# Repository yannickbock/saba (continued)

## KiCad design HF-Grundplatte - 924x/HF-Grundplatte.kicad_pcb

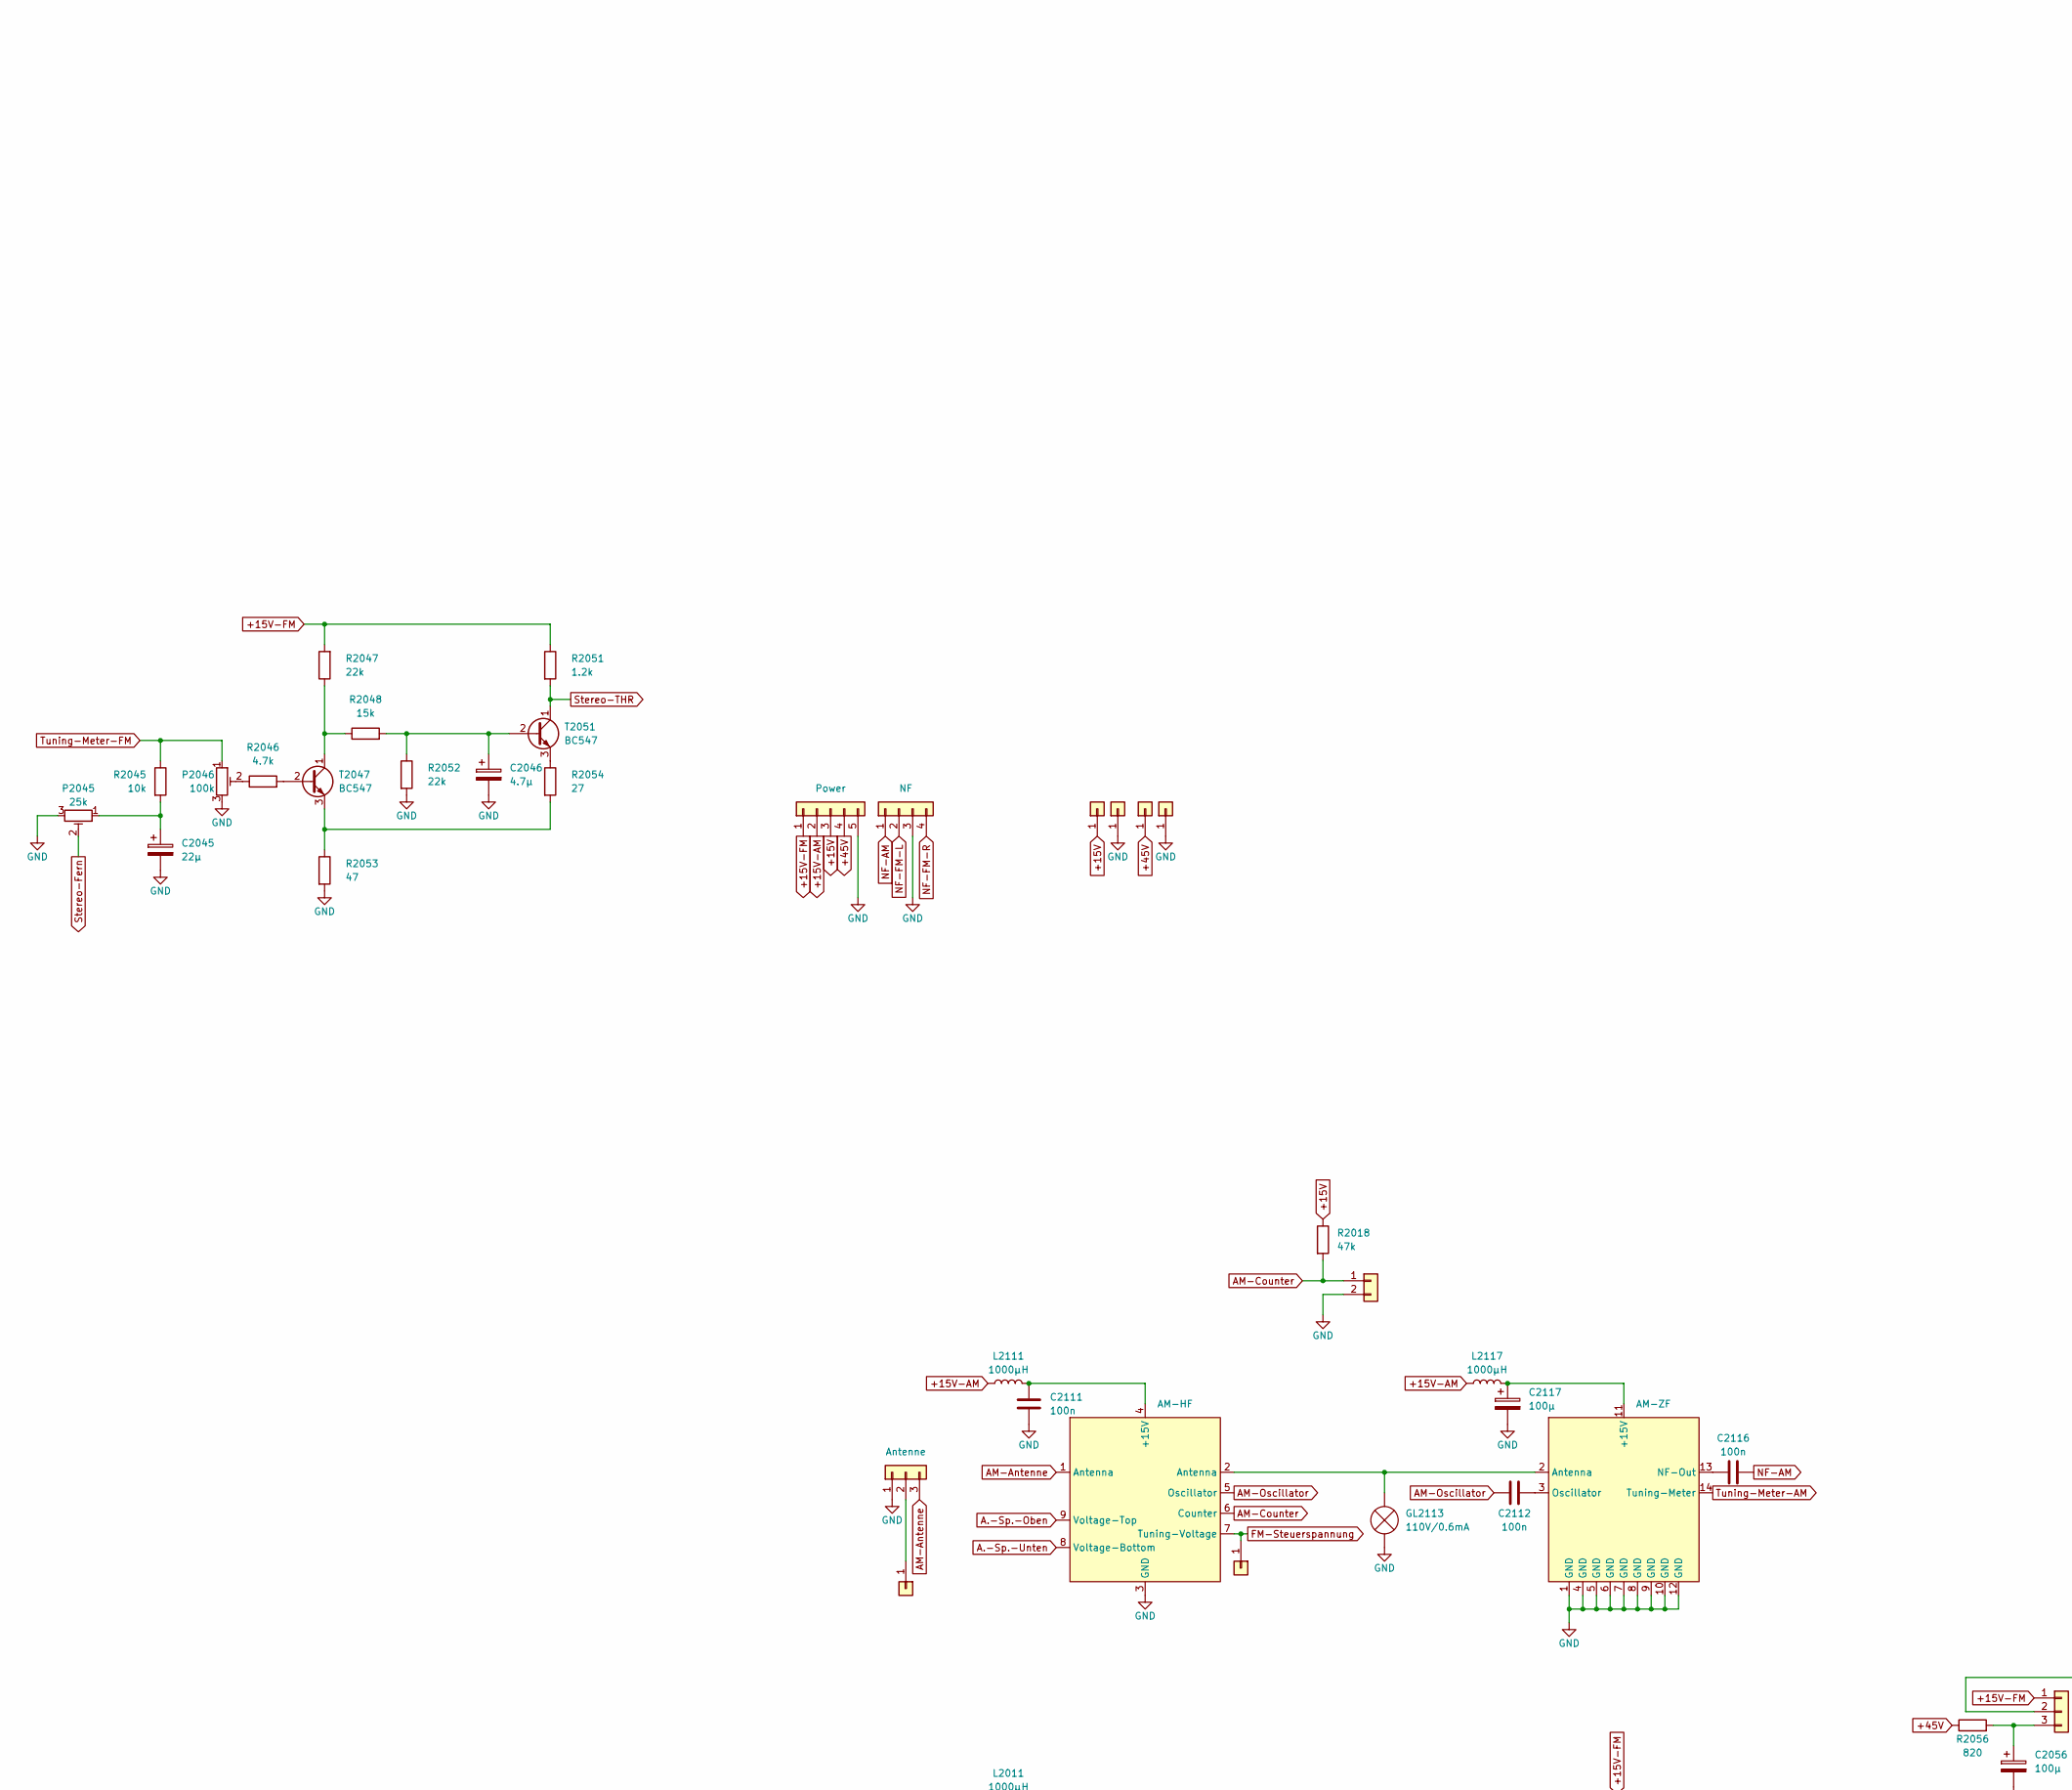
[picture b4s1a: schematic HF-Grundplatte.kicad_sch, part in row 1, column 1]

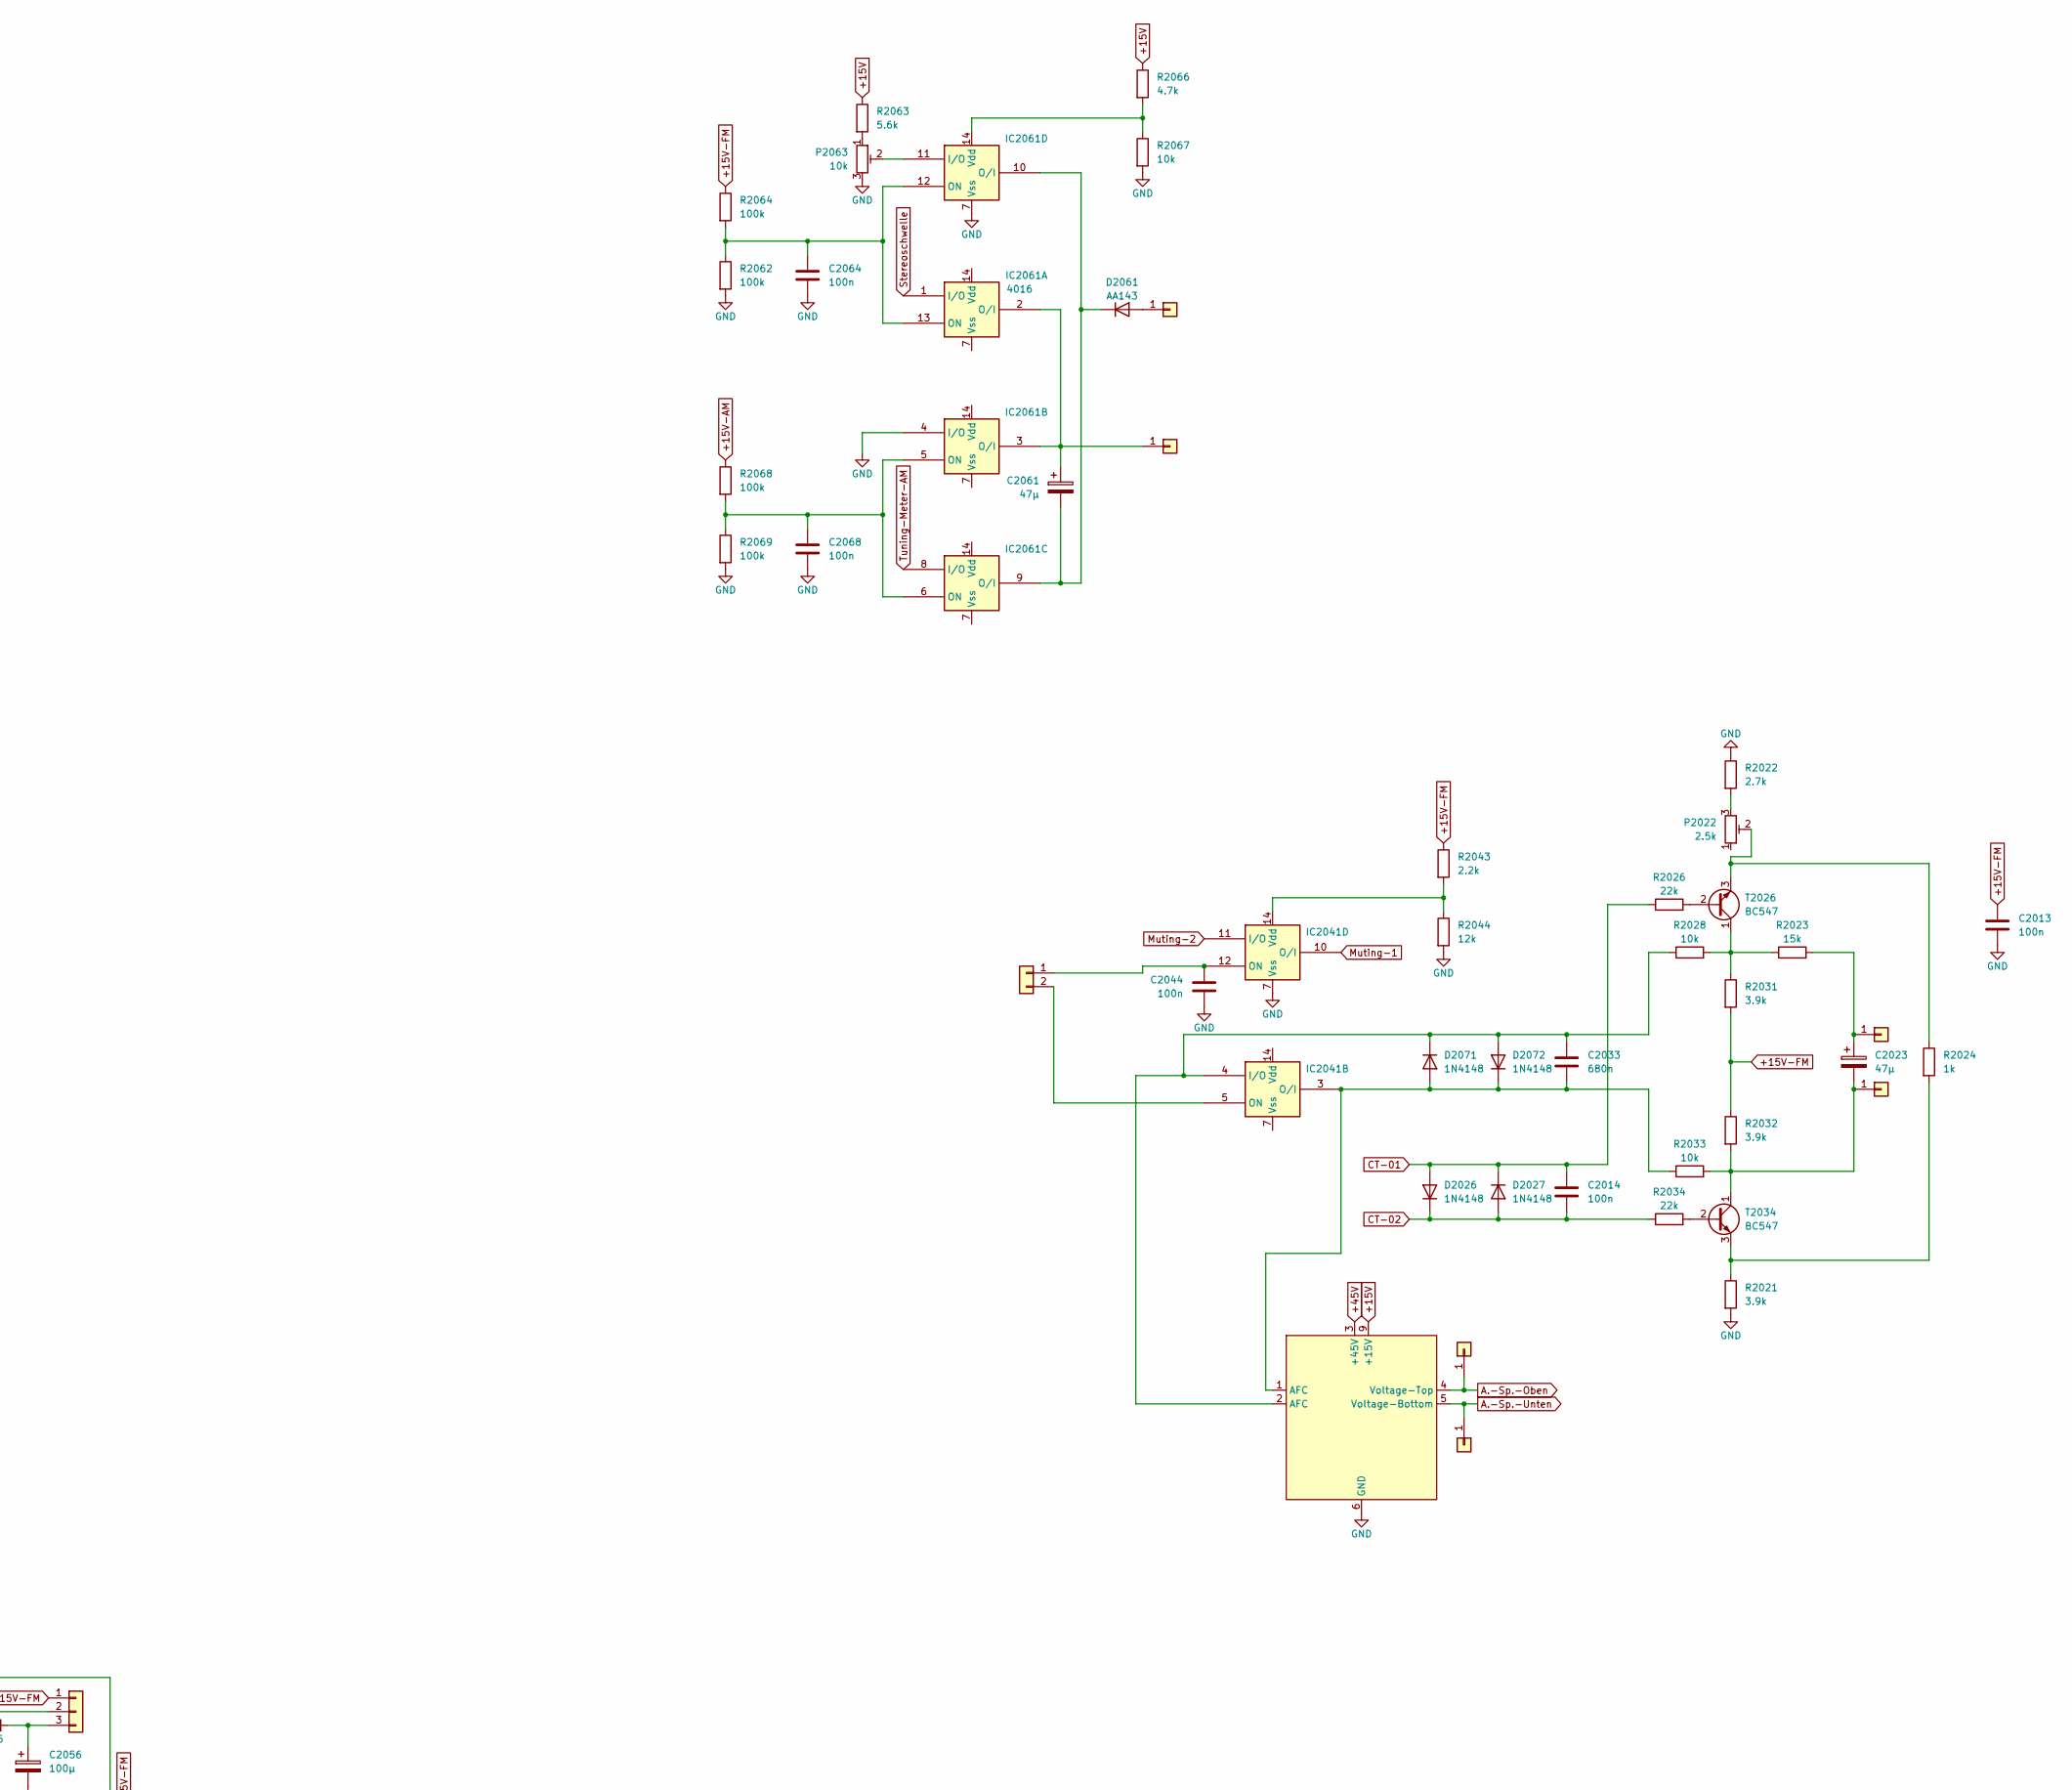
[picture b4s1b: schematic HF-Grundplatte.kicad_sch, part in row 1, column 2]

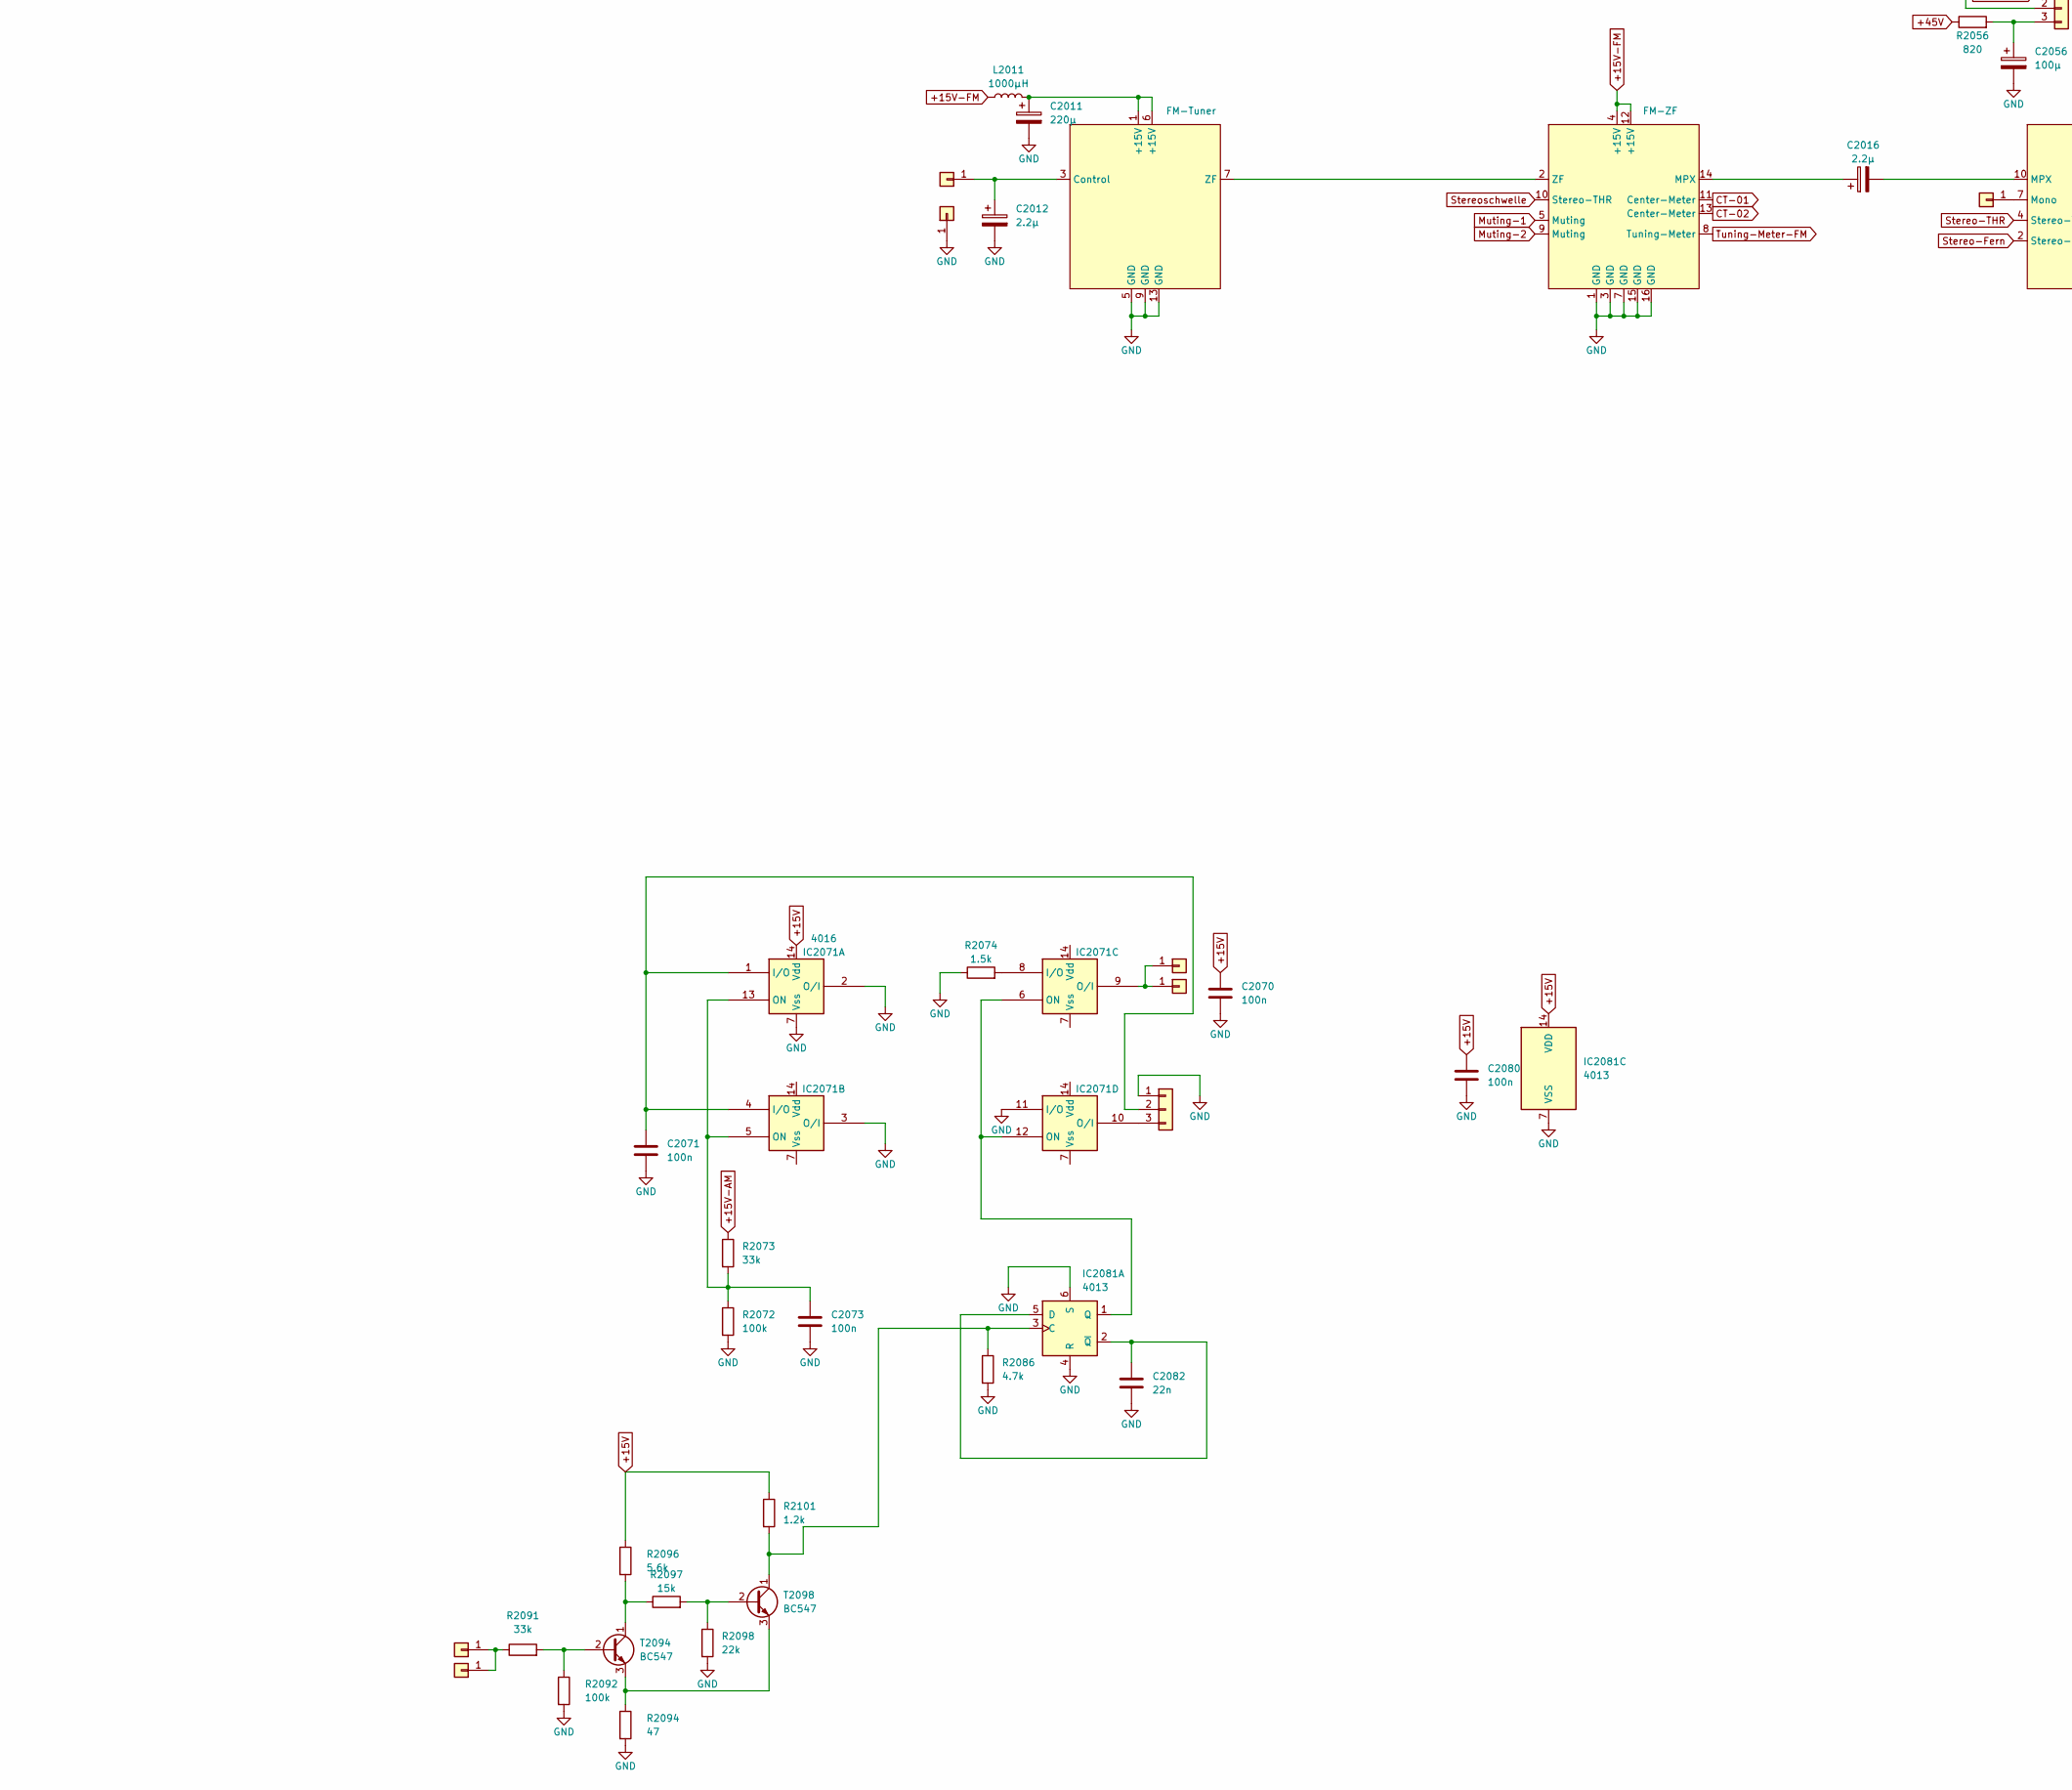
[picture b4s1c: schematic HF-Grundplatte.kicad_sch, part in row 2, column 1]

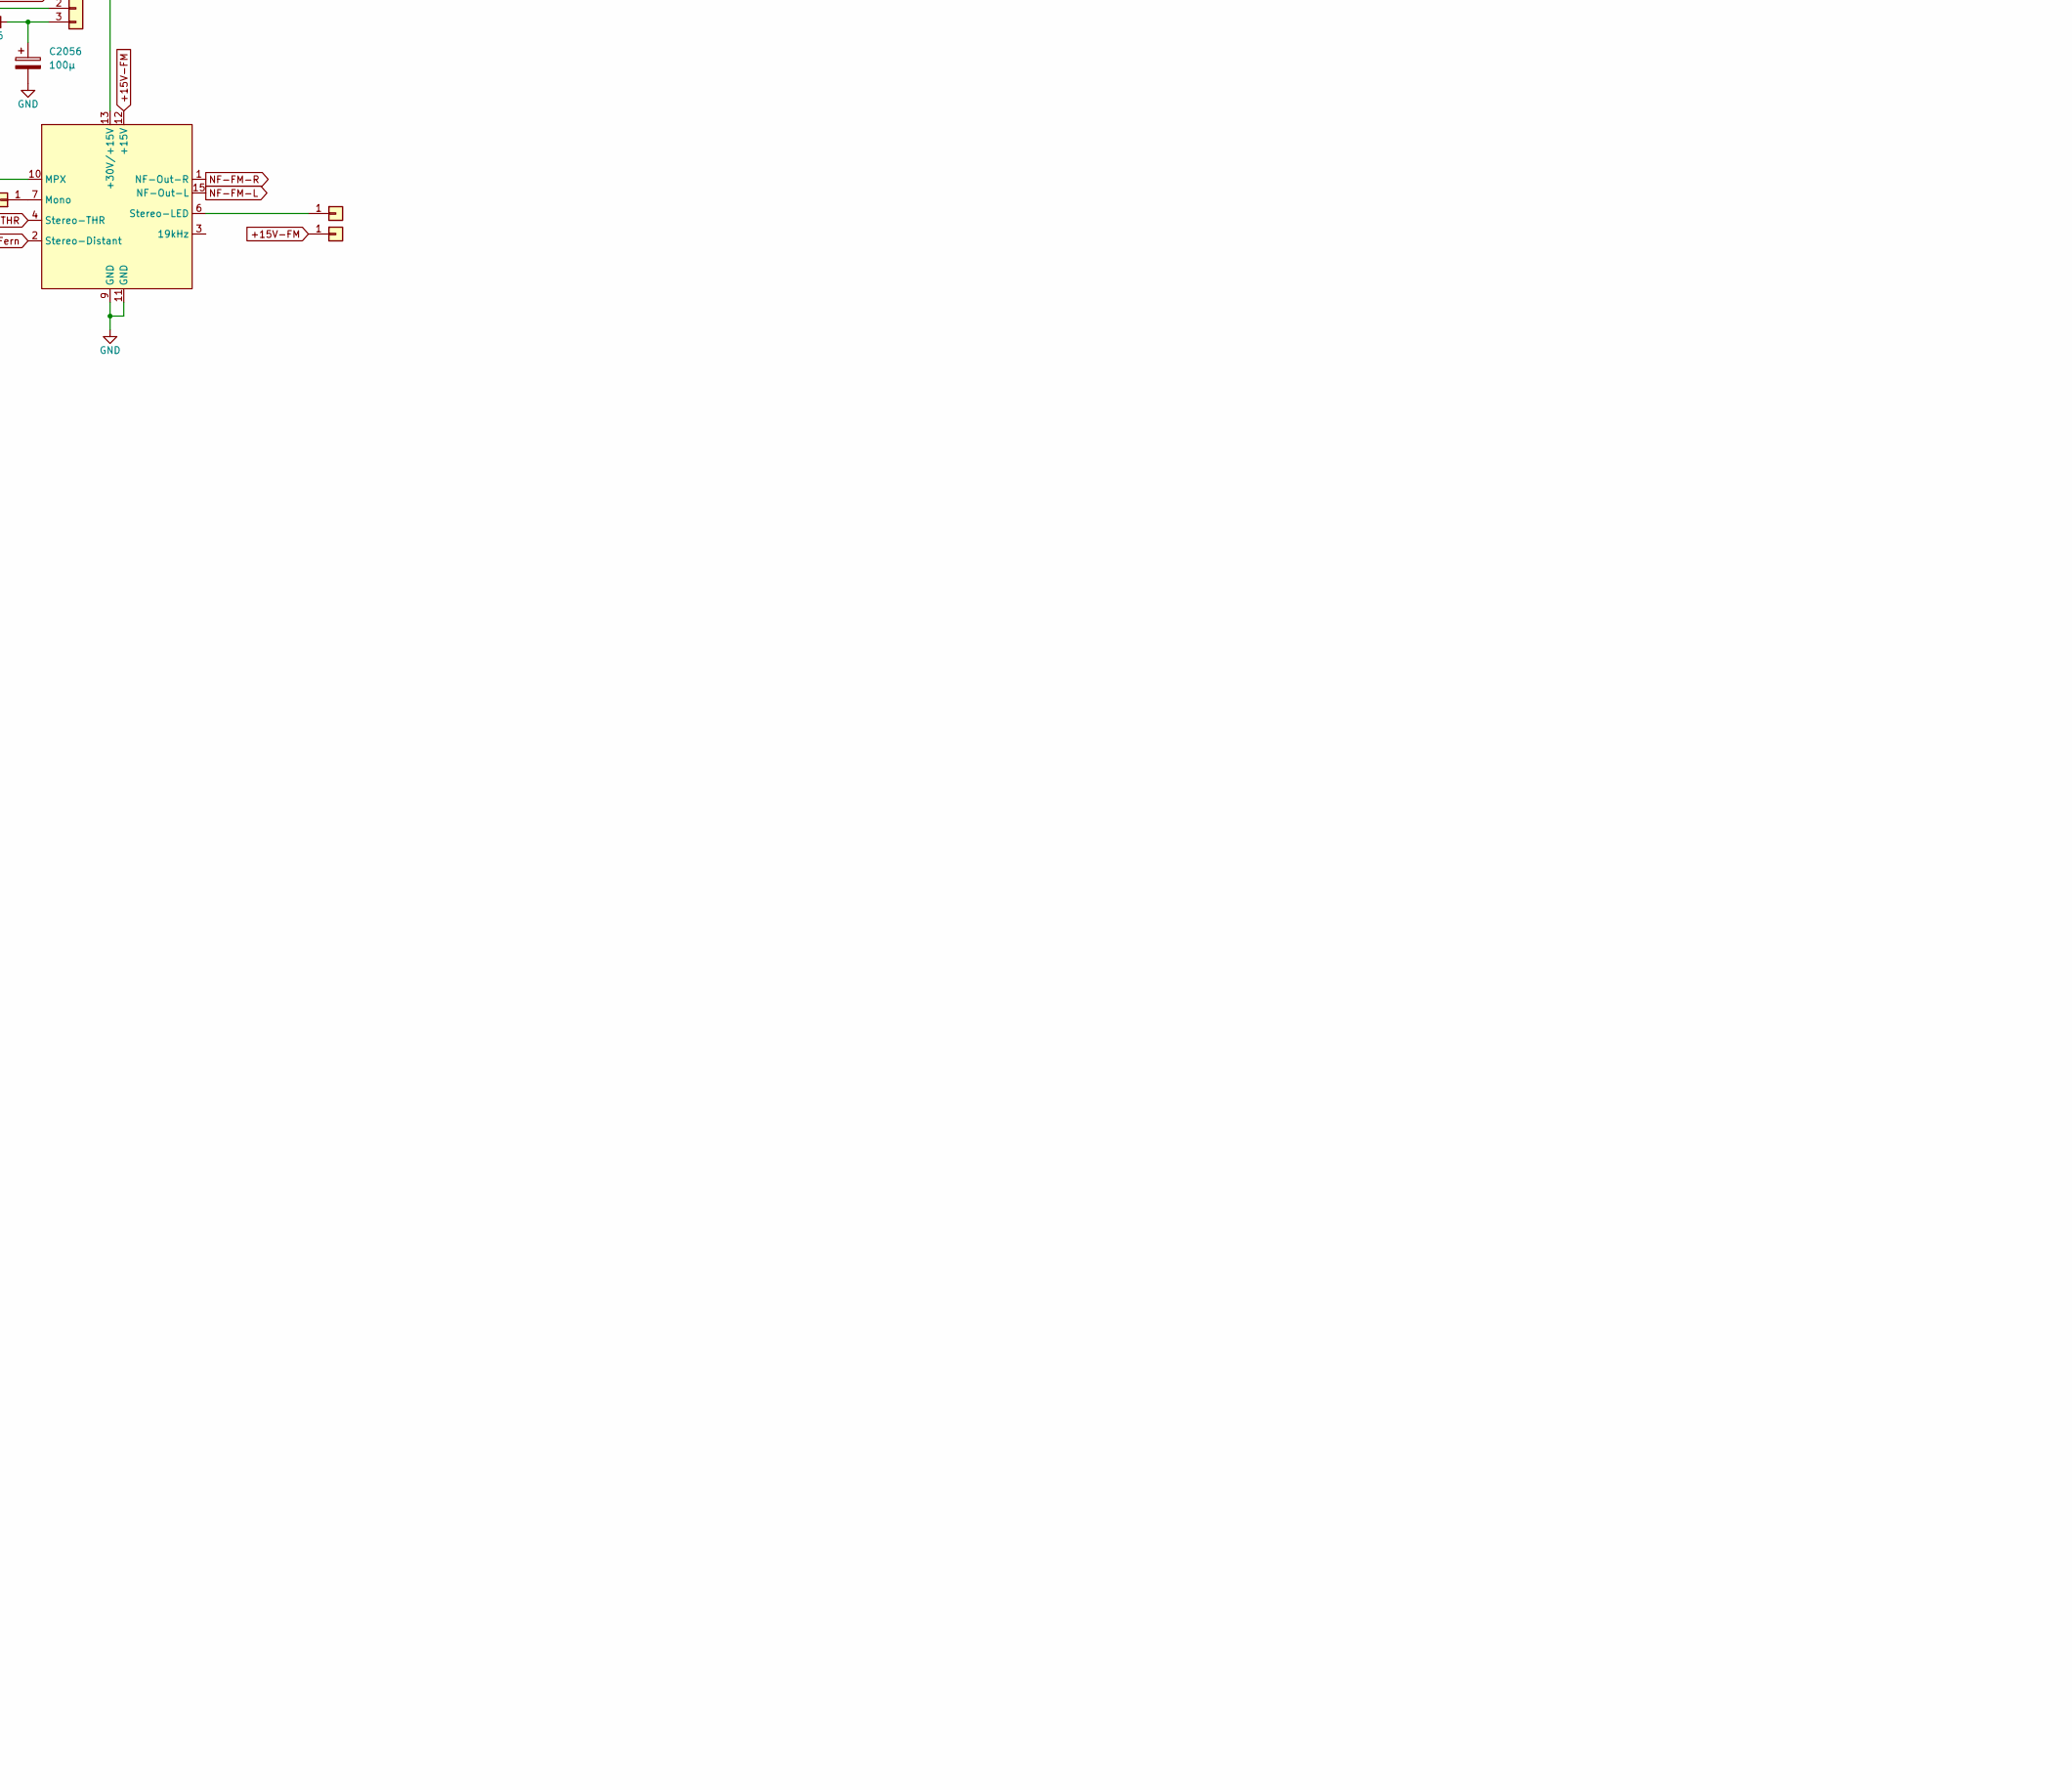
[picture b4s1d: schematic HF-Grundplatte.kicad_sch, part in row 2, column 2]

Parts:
C2011: 220µ; CP_Radial_D8.0mm_P3.50mm
C2012: 2.2µ; CP_Radial_D5.0mm_P2.00mm
C2013, C2014, C2044, C2064, C2068, C2070, C2071, C2073, C2080, C2111, C2112, C2116: 100n; C_Rect_L7.2mm_W2.5mm_P5.00mm_FKS2_FKP2_MKS2_MKP2
C2016: 2.2µ; C_Rect_L7.2mm_W7.2mm_P5.00mm_FKS2_FKP2_MKS2_MKP2
C2023, C2061: 47µ; CP_Radial_D5.0mm_P2.00mm
C2033: 680n; C_Rect_L7.2mm_W2.5mm_P5.00mm_FKS2_FKP2_MKS2_MKP2
C2045: 22µ; CP_Radial_D5.0mm_P2.00mm
C2046: 4.7µ; CP_Radial_D5.0mm_P2.00mm
C2056: 100µ; CP_Radial_D10.0mm_P5.00mm
C2082: 22n; C_Disc_D4.7mm_W2.5mm_P5.00mm
C2117: 100µ; CP_Radial_D6.3mm_P2.50mm
D2026, D2027, D2071, D2072: 1N4148; D_DO-35_SOD27_P10.16mm_Horizontal
D2061: AA143; D_DO-35_SOD27_P10.16mm_Horizontal
GL2113: 110V/0.6mA; Glimmlampe
IC2041, IC2061, IC2071: 4016; DIP-14_W7.62mm
IC2081: 4013; DIP-14_W7.62mm
J1: FM-Tuner
J2: AM-HF
J3: AM-ZF
J4: Stereo-Decoder
J5: Abstimmspannung
J6: FM-ZF
J7: Antenne; AM-Antenne
J8: Conn_01x01; Pin_D1.3mm_L11.0mm
J9, J10, J13, J26, J27: br; Pin_D1.3mm_L11.0mm
J11: NF; Conn_01x04
J12: Power; Conn_01x05
J14, J34, J35, J36, J37: sw; Pin_D1.3mm_L11.0mm
J15: rt; Pin_D1.3mm_L11.0mm
J16: or; Pin_D1.3mm_L11.0mm
J17: gn; Pin_D1.3mm_L11.0mm
J18: ge; Pin_D1.3mm_L11.0mm
J19: rt; Conn_01x01
J20: Conn_01x03; SolderPads_Bridge_01x03_2.5mm
J21, J22, J23, J24, J25: rt; TestPoint_Loop_D1.80mm_Drill1.0mm_Beaded
J28: Conn_01x02; Conn_01x02_5mm
J29: Conn_01x03; Conn_01x03_5mm
J30: Conn_01x02
L2011, L2111, L2117: 1000µH; L_Radial_D7.5mm_P5.00mm_Fastron_07P
P2022: 2.5k; Potentiometer_Piher_PT-10-V10_Vertical
P2045: 25k; Potentiometer_Piher_PT-10-V10_Vertical
P2046: 100k; Potentiometer_Piher_PT-15-H05_Horizontal
P2063: 10k; Potentiometer_Piher_PT-10-V10_Vertical
R2018: 47k; R_Axial_DIN0207_L6.3mm_D2.5mm_P10.16mm_Horizontal
R2021, R2031, R2032: 3.9k; R_Axial_DIN0207_L6.3mm_D2.5mm_P10.16mm_Horizontal
R2022: 2.7k; R_Axial_DIN0207_L6.3mm_D2.5mm_P10.16mm_Horizontal
R2023, R2048, R2097: 15k; R_Axial_DIN0207_L6.3mm_D2.5mm_P10.16mm_Horizontal
R2024: 1k; R_Axial_DIN0207_L6.3mm_D2.5mm_P10.16mm_Horizontal
R2026, R2034, R2047, R2052, R2098: 22k; R_Axial_DIN0207_L6.3mm_D2.5mm_P10.16mm_Horizontal
R2028, R2033, R2045, R2067: 10k; R_Axial_DIN0207_L6.3mm_D2.5mm_P10.16mm_Horizontal
R2043: 2.2k; R_Axial_DIN0207_L6.3mm_D2.5mm_P10.16mm_Horizontal
R2044: 12k; R_Axial_DIN0207_L6.3mm_D2.5mm_P10.16mm_Horizontal
R2046, R2066, R2086: 4.7k; R_Axial_DIN0207_L6.3mm_D2.5mm_P10.16mm_Horizontal
R2051, R2101: 1.2k; R_Axial_DIN0207_L6.3mm_D2.5mm_P10.16mm_Horizontal
R2053, R2094: 47; R_Axial_DIN0207_L6.3mm_D2.5mm_P10.16mm_Horizontal
R2054: 27; R_Axial_DIN0207_L6.3mm_D2.5mm_P10.16mm_Horizontal
R2056: 820; R_Axial_DIN0207_L6.3mm_D2.5mm_P10.16mm_Horizontal
R2062, R2064, R2068, R2069, R2072, R2092: 100k; R_Axial_DIN0207_L6.3mm_D2.5mm_P10.16mm_Horizontal
R2063, R2096: 5.6k; R_Axial_DIN0207_L6.3mm_D2.5mm_P10.16mm_Horizontal
R2073, R2091: 33k; R_Axial_DIN0207_L6.3mm_D2.5mm_P10.16mm_Horizontal
R2074: 1.5k; R_Axial_DIN0207_L6.3mm_D2.5mm_P10.16mm_Horizontal
T2026, T2034, T2047, T2051, T2094, T2098: BC547; TO-92_Wide

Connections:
+15V: C2070.1, C2080.1, IC2071.14 (Vdd), IC2081.14 (VDD), J5.9 (+15V), J12.3, J34.1, R2018.1, R2063.1, R2066.1, R2096.1, R2101.1
+15V-AM: J12.2, L2111.1, L2117.1, R2068.1, R2073.1
+15V-FM: C2013.1, J4.12 (+15V), J6.4 (+15V), J6.12 (+15V), J12.1, J18.1, J20.1, L2011.2, R2031.2, R2032.1, R2043.1, R2047.2, R2051.1, R2064.1
+45V: J5.3 (+45V), J12.4, J36.1, R2056.1
A.-Sp.-Oben: J2.9 (Voltage-Top), J5.4 (Voltage-Top), J21.1
A.-Sp.-Unten: J2.8 (Voltage-Bottom), J5.5 (Voltage-Bottom), J22.1
AM-Antenne: J2.1 (Antenna), J7.3
AM-Counter: J2.6 (Counter), J28.1, R2018.2
AM-Oscillator: C2112.2, J2.5 (Oscillator)
CT-01: C2014.1, D2026.2 (A), D2027.1 (K), J6.11 (Center-Meter), R2026.1
CT-02: C2014.2, D2026.1 (K), D2027.2 (A), J6.13 (Center-Meter), R2034.1
FM-Steuerspannung: J2.7 (Tuning-Voltage), J25.1
GND: C2011.2, C2012.2, C2013.2, C2044.2, C2045.2, C2046.2, C2056.2, C2064.2, C2068.2, C2070.2, C2071.2, C2073.2, C2080.2, C2082.2, C2111.2, C2117.2, GL2113.1 (-), IC2041.7 (Vss), IC2061.4 (I/O), IC2061.7 (Vss), IC2071.2 (O/I), IC2071.3 (O/I), IC2071.7 (Vss), IC2071.11 (I/O), IC2081.4 (R), IC2081.6 (S), IC2081.7 (VSS), J1.5 (GND), J1.9 (GND), J1.13 (GND), J2.3 (GND), J3.1 (GND), J3.4 (GND), J3.5 (GND), J3.6 (GND), J3.7 (GND), J3.8 (GND), J3.9 (GND), J3.10 (GND), J3.12 (GND), J4.9 (GND), J4.11 (GND), J5.6 (GND), J6.1 (GND), J6.3 (GND), J6.7 (GND), J6.15 (GND), J6.16 (GND), J7.1, J11.3, J12.5, J24.1, J28.2, J29.1, J35.1, J37.1, P2045.3, P2046.3, P2063.3, R2021.2, R2022.1, R2044.2, R2052.2, R2053.2, R2062.2, R2067.2, R2069.2, R2072.2, R2074.1, R2086.2, R2092.2, R2094.2, R2098.2
Muting-1: IC2041.10 (O/I), J6.5 (Muting)
Muting-2: IC2041.11 (I/O), J6.9 (Muting)
NF-AM: C2116.2, J11.1
NF-FM-L: J4.15 (NF-Out-L), J11.2
NF-FM-R: J4.1 (NF-Out-R), J11.4
unnamed: C2011.1, J1.1 (+15V), J1.6 (+15V), L2011.1
unnamed: C2045.1, P2045.1, R2045.2
unnamed: D2061.2 (A), J14.1
unnamed: C2061.2, D2061.1 (K), IC2061.9 (O/I), IC2061.10 (O/I)
unnamed: C2033.2, D2071.2 (A), D2072.1 (K), IC2041.3 (O/I), J5.1 (AFC), R2033.1
unnamed: C2033.1, D2071.1 (K), D2072.2 (A), IC2041.4 (I/O), J5.2 (AFC), R2028.1
unnamed: GL2113.2 (+), J2.2 (Antenna), J3.2 (Antenna)
unnamed: IC2041.5 (ON), J30.2
unnamed: C2044.1, IC2041.12 (ON), J30.1
unnamed: IC2041.14 (Vdd), R2043.2, R2044.1
unnamed: C2064.1, IC2061.12 (ON), IC2061.13 (ON), R2062.1, R2064.2
unnamed: C2061.1, IC2061.2 (O/I), IC2061.3 (O/I), J13.1
unnamed: C2068.1, IC2061.5 (ON), IC2061.6 (ON), R2068.2, R2069.1
unnamed: IC2061.11 (I/O), P2063.2
unnamed: IC2061.14 (Vdd), R2066.2, R2067.1
unnamed: C2071.1, IC2071.1 (I/O), IC2071.4 (I/O), J29.2
unnamed: C2073.1, IC2071.5 (ON), IC2071.13 (ON), R2072.1, R2073.2
unnamed: IC2071.8 (I/O), R2074.2
unnamed: IC2071.6 (ON), IC2071.12 (ON), IC2081.1 (Q)
unnamed: IC2071.9 (O/I), J10.1, J26.1
unnamed: IC2071.10 (O/I), J29.3
unnamed: IC2081.3 (C), R2086.1, R2101.2, T2098.1 (C)
unnamed: C2082.1, IC2081.2 (~Q), IC2081.5 (D)
unnamed: C2012.1, J1.3 (Control), J23.1
unnamed: J1.7 (ZF), J6.2 (ZF)
unnamed: C2111.1, J2.4 (+15V), L2111.2
unnamed: C2117.1, J3.11 (+15V), L2117.2
unnamed: C2116.1, J3.13 (NF-Out)
unnamed: C2112.1, J3.3 (Oscillator)
unnamed: C2016.2, J4.10 (MPX)
unnamed: C2016.1, J6.14 (MPX)
unnamed: J7.2, J8.1
unnamed: C2023.2, J15.1, R2032.2, R2033.2, T2034.1 (C)
unnamed: C2023.1, J16.1, R2023.2
unnamed: J4.6 (Stereo-LED), J17.1
unnamed: J4.7 (Mono), J19.1
unnamed: J4.13 (+30V/+15V), J20.2
unnamed: C2056.1, J20.3, R2056.2
unnamed: J9.1, J27.1, R2091.1
unnamed: P2022.3, R2022.2
unnamed: P2046.2, R2046.1
unnamed: P2063.1, R2063.2
unnamed: R2026.2, T2026.2 (B)
unnamed: R2023.1, R2028.2, R2031.1, T2026.1 (C)
unnamed: P2022.2, R2024.1, T2026.3 (E)
unnamed: R2034.2, T2034.2 (B)
unnamed: R2021.1, R2024.2, T2034.3 (E)
unnamed: R2046.2, T2047.2 (B)
unnamed: R2047.1, R2048.1, T2047.1 (C)
unnamed: R2053.1, R2054.2, T2047.3 (E)
unnamed: C2046.1, R2048.2, R2052.1, T2051.2 (B)
unnamed: R2054.1, T2051.3 (E)
unnamed: R2091.2, R2092.1, T2094.2 (B)
unnamed: R2096.2, R2097.1, T2094.1 (C)
unnamed: R2094.1, T2094.3 (E), T2098.3 (E)
unnamed: R2097.2, R2098.1, T2098.2 (B)
Stereo-Fern: J4.2 (Stereo-Distant), P2045.2
Stereo-THR: J4.4 (Stereo-THR), R2051.2, T2051.1 (C)
Stereoschwelle: IC2061.1 (I/O), J6.10 (Stereo-THR)
Tuning-Meter-AM: IC2061.8 (I/O), J3.14 (Tuning-Meter)
Tuning-Meter-FM: J6.8 (Tuning-Meter), P2046.1, R2045.1
